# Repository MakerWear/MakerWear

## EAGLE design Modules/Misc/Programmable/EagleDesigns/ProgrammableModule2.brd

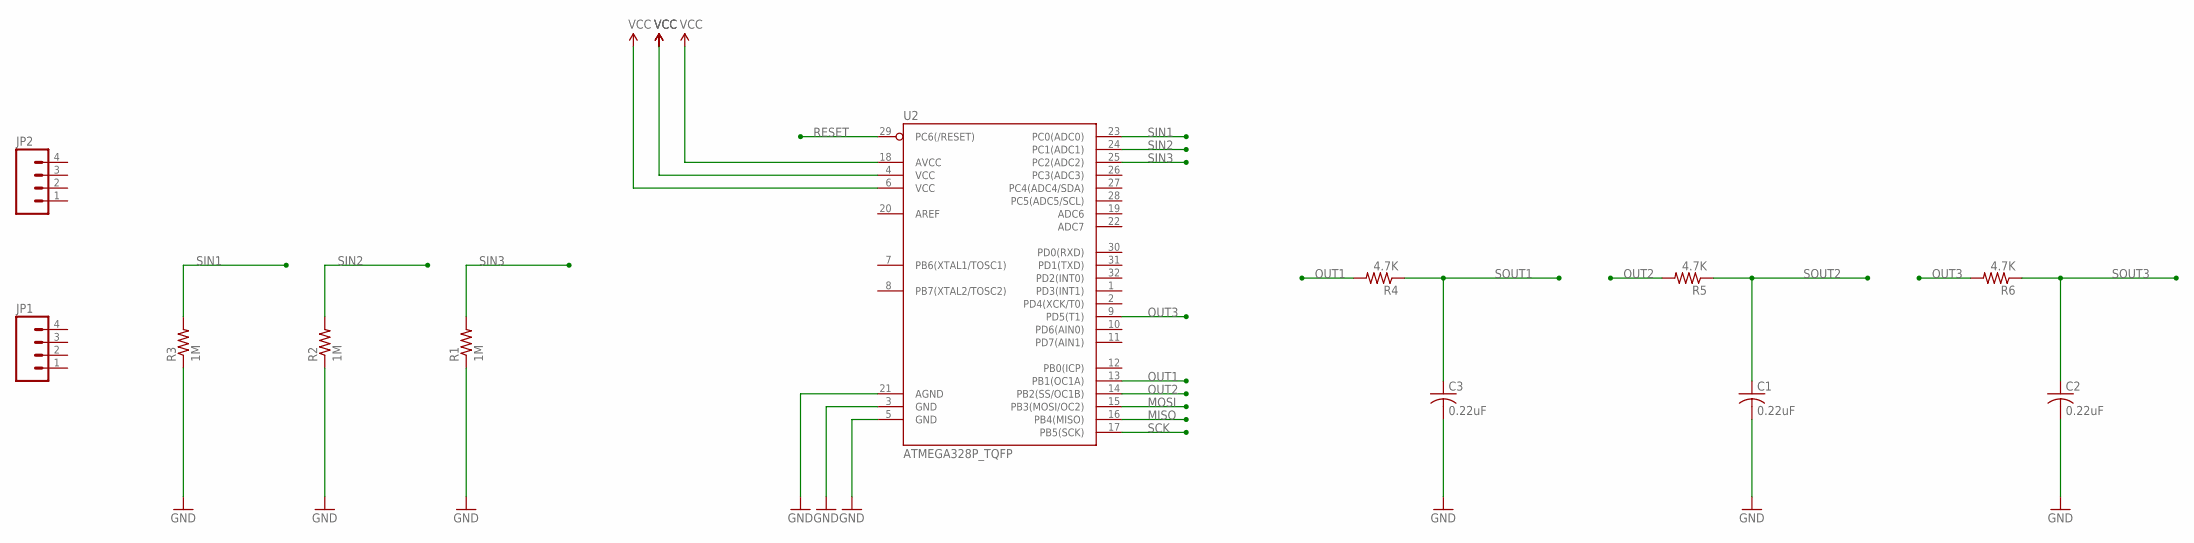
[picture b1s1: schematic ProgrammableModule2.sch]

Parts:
C1, C2, C3: 0.22uF; C0603
JP1, JP2: M04PTH; 1X04
R1, R2, R3: 1M; R0603
R4, R5, R6: 4.7K; R0603
U2: ATMEGA328P_TQFP; TQFP32-08

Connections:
GND: C1.2, C2.2, C3.2, R1.1, R2.1, R3.1, U2.3 (GND), U2.5 (GND), U2.21 (AGND)
MISO: U2.16 (PB4(MISO))
MOSI: U2.15 (PB3(MOSI/OC2))
OUT1: R4.2, U2.13 (PB1(OC1A))
OUT2: R5.2, U2.14 (PB2(SS/OC1B))
OUT3: R6.2, U2.9 (PD5(T1))
RESET: U2.29 (PC6(/RESET))
SCK: U2.17 (PB5(SCK))
SIN1: R3.2, U2.23 (PC0(ADC0))
SIN2: R2.2, U2.24 (PC1(ADC1))
SIN3: R1.2, U2.25 (PC2(ADC2))
SOUT1: C3.1, R4.1
SOUT2: C1.1, R5.1
SOUT3: C2.1, R6.1
VCC: U2.4 (VCC), U2.6 (VCC), U2.18 (AVCC)

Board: 2 copper layers, 12 parts (0 on the bottom side), 11 nets, no tracks yet.

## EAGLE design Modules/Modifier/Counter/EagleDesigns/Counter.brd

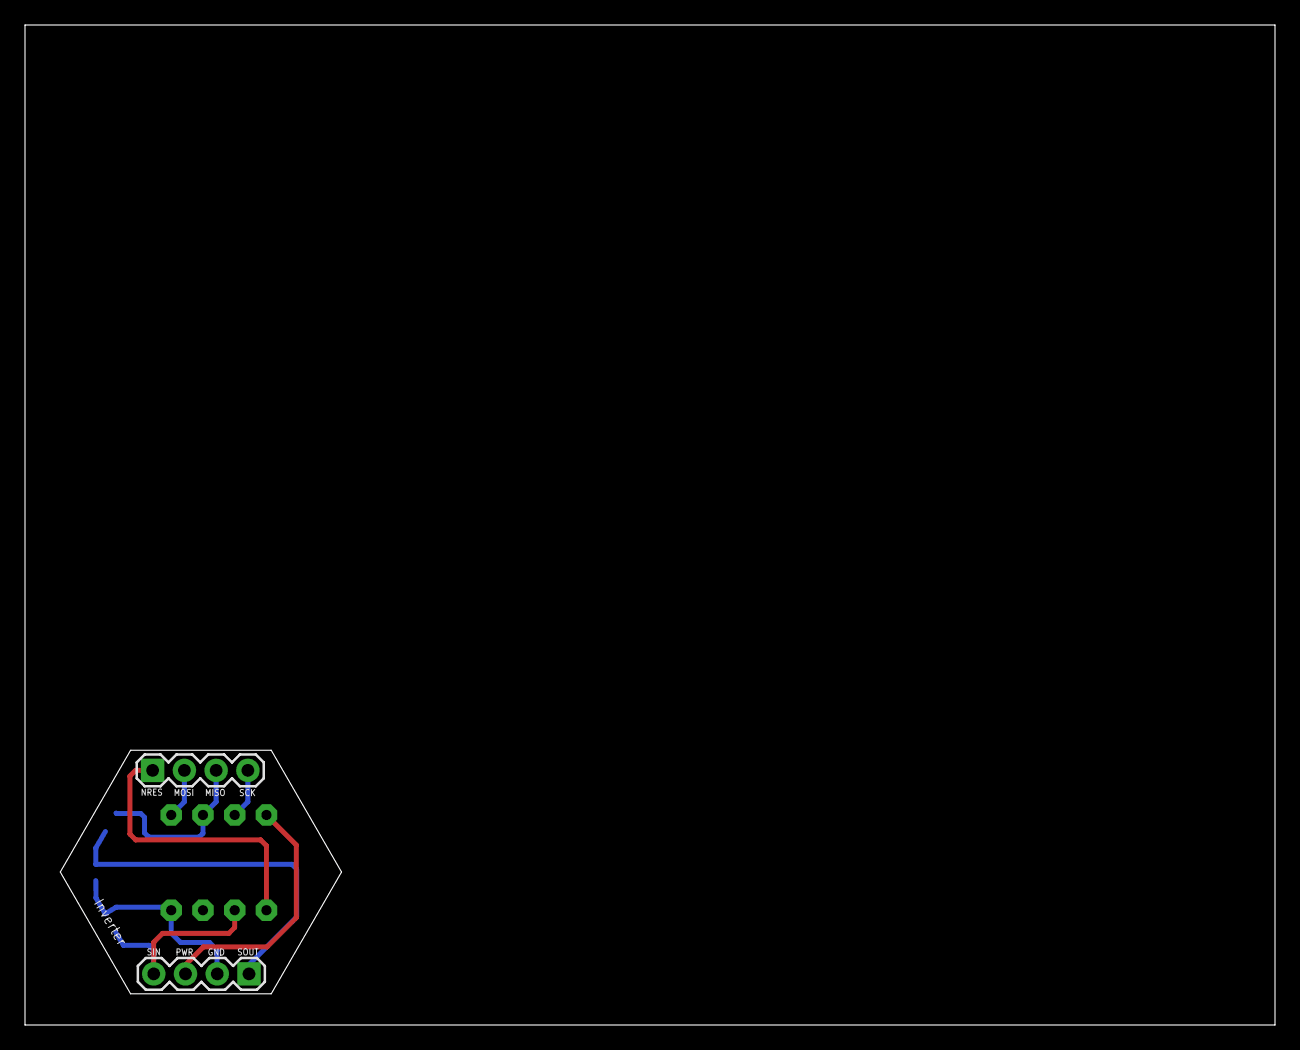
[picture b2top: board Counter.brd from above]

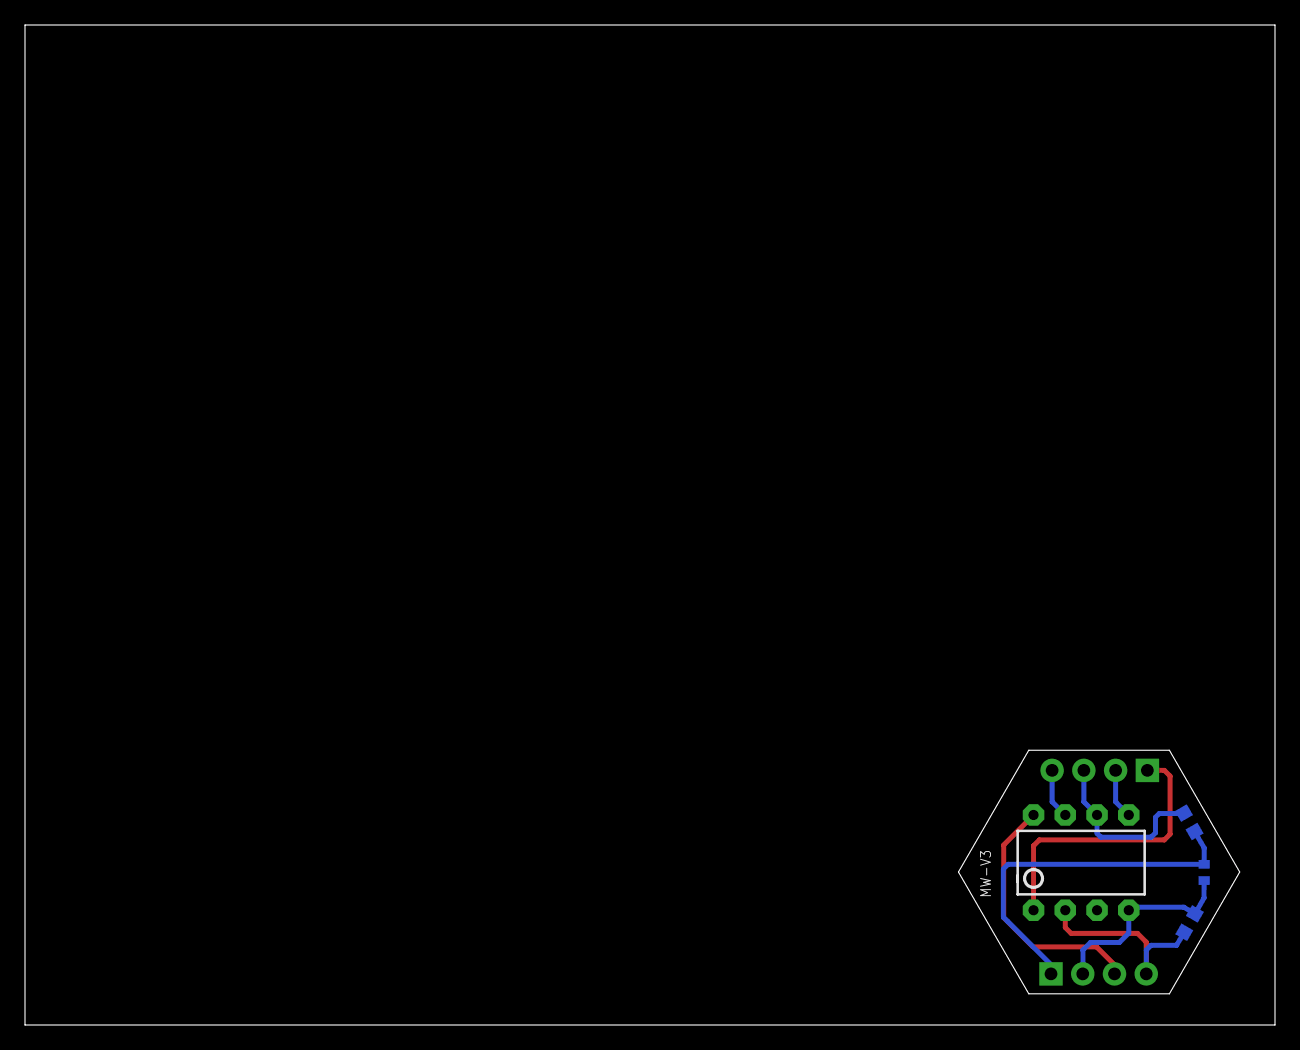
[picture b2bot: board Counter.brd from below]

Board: 2 copper layers, 100.0 x 80.0 mm, 6 parts (4 on the bottom side), 8 nets.

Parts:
C1: 0.22uF; C0402
JP1, JP2: 1X04
R1: 1M; R0603
R2: 4.7K; R0603
U1: TINY85-20-DIP; DIP08

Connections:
1X3SIN: JP1.4, R1.2, U1.2
1X3SOUT: C1.2, JP1.1, R2.1
GND: C1.1, JP1.2, R1.1, U1.4
MOSI: JP2.2, U1.5
NRES: JP2.1, U1.1
OUT(MISO): JP2.3, R2.2, U1.6
SCK: JP2.4, U1.7
VCC: JP1.3, U1.8

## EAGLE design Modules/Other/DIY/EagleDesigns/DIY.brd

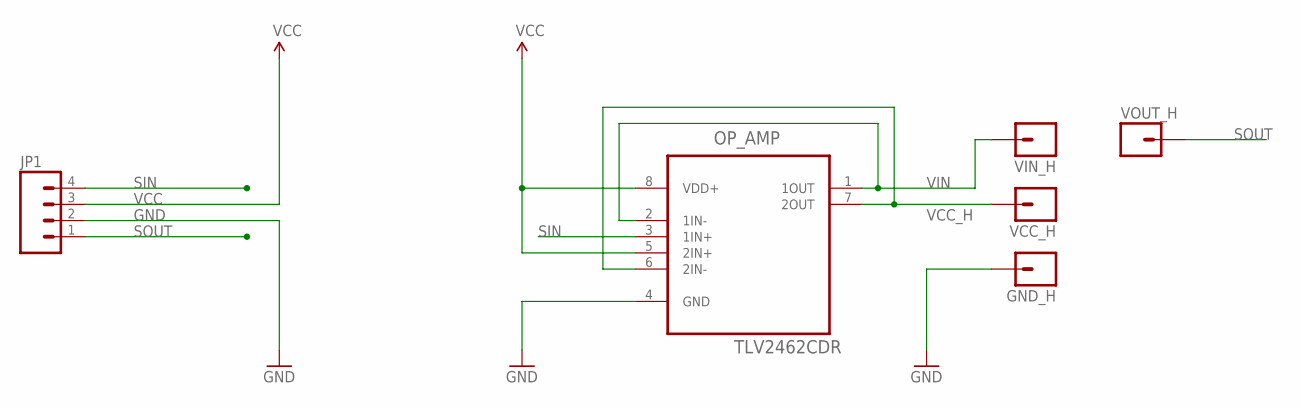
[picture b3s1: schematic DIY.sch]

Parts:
GND_H: M01PTH; 1X01
JP1: M04PTH; 1X04
OP_AMP: TLV2462CDR; SOIC127P600X175-8N
VCC_H: M01PTH; 1X01
VIN_H: M01PTH; 1X01
VOUT_H: M01PTH; 1X01

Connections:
GND: GND_H.1, JP1.2, OP_AMP.4 (GND)
SIN: JP1.4, OP_AMP.3 (1IN+)
SOUT: JP1.1, VOUT_H.1
VCC: JP1.3, OP_AMP.5 (2IN+), OP_AMP.8 (VDD+)
VCC_H: OP_AMP.6 (2IN-), OP_AMP.7 (2OUT), VCC_H.1
VIN: OP_AMP.1 (1OUT), OP_AMP.2 (1IN-), VIN_H.1

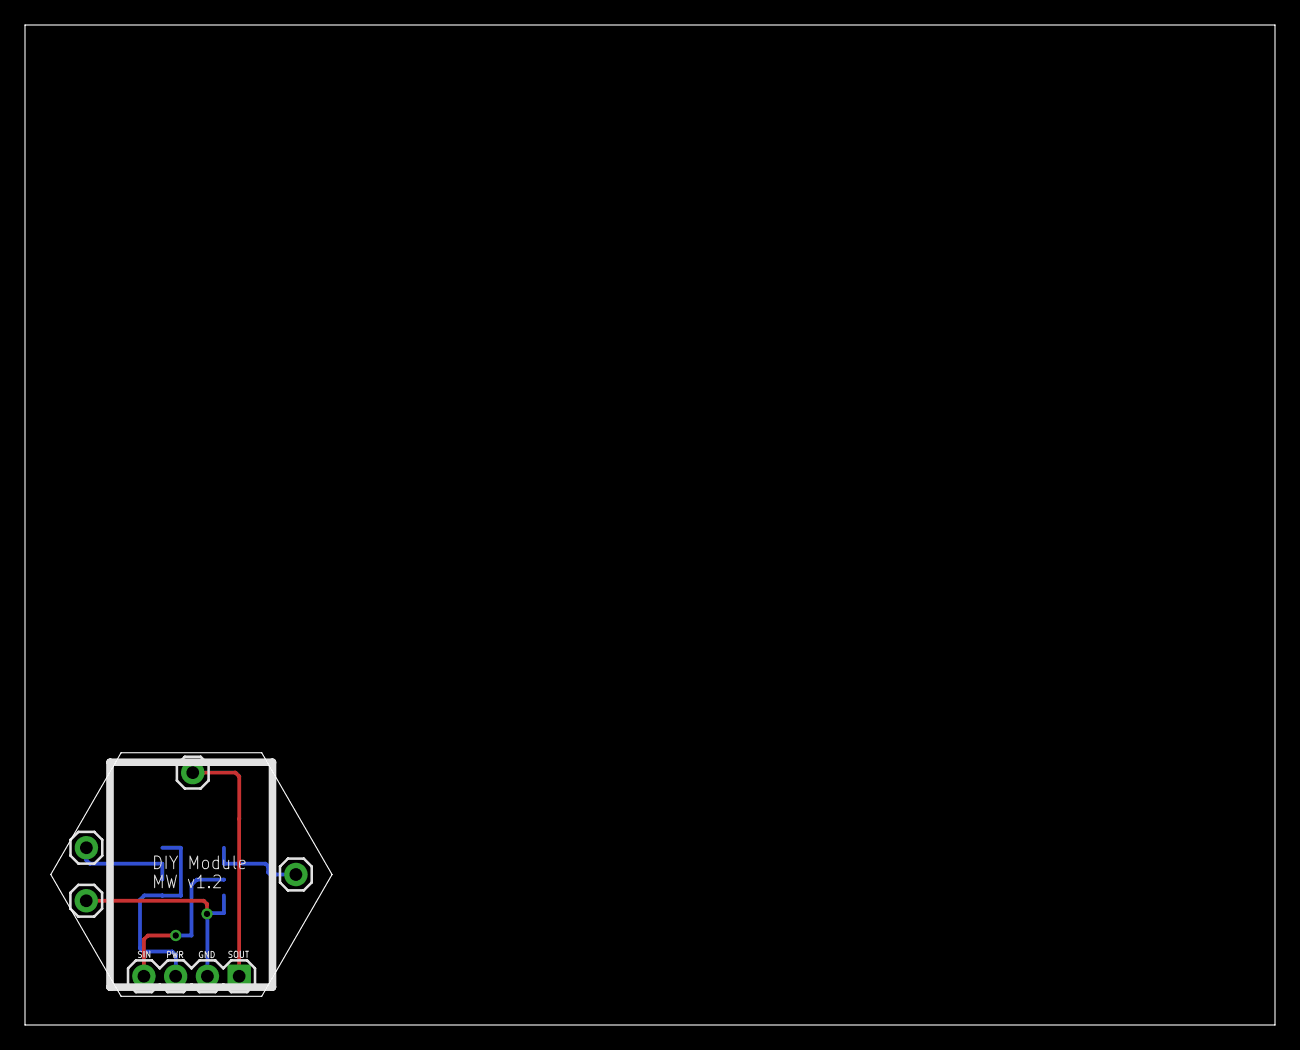
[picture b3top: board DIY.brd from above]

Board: 2 copper layers, 100.0 x 80.0 mm, 6 parts (1 on the bottom side), 6 nets.

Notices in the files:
parts and their libraries:
SparkFun-Connectors: Licensing: Creative Commons ShareAlike 4.0 International - https://creativecommons.org/licenses/by-sa/4.0
